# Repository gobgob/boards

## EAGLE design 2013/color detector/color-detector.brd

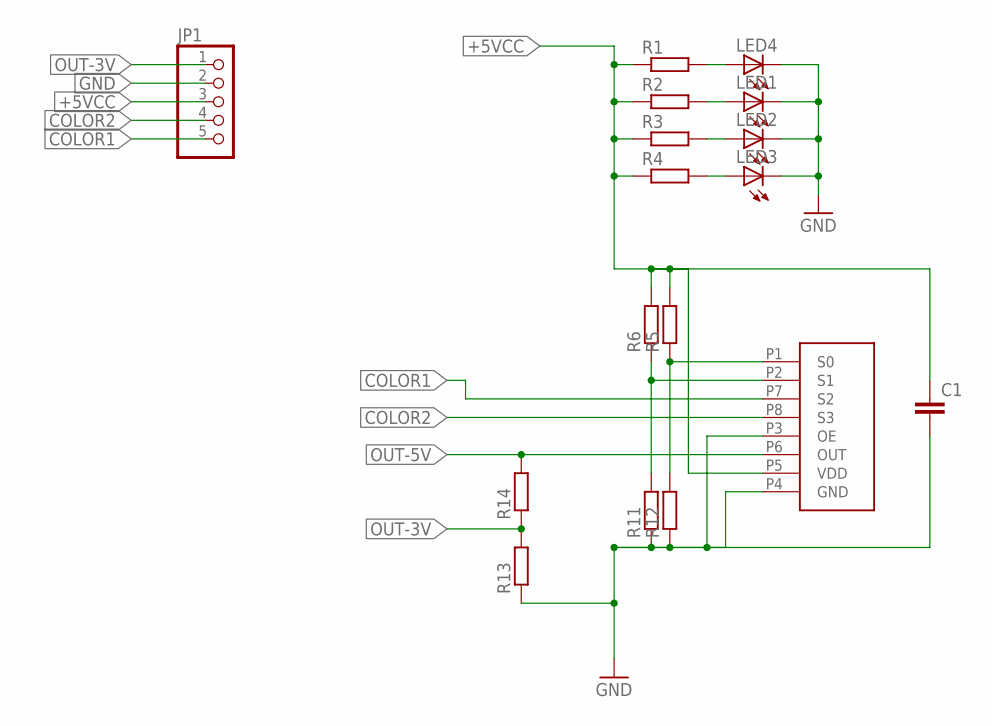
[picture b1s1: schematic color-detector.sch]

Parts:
C1: C-EUC0805; C0805
JP1: PINHD-1X5/90; 1X05/90
LED1, LED2, LED3, LED4: LED3MM
R1, R2, R3, R4, R13, R14: R-EU_R0805; R0805
R5, R6, R11, R12: R-EU_R0402; R0402
U$1: TCS3200; SOIC8

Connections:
+5VCC: C1.1, JP1.3, R1.1, R2.1, R3.1, R4.1, R5.2, R6.2, U$1.P5 (VDD)
COLOR1: JP1.5, U$1.P7 (S2)
COLOR2: JP1.4, U$1.P8 (S3)
GND: C1.2, JP1.2, LED1.K (C), LED2.K (C), LED3.K (C), LED4.K (C), R11.1, R12.1, R13.1, U$1.P3 (OE), U$1.P4 (GND)
unnamed: LED4.A, R1.2
unnamed: LED1.A, R2.2
unnamed: LED2.A, R3.2
unnamed: LED3.A, R4.2
unnamed: R5.1, R12.2, U$1.P1 (S0)
unnamed: R6.1, R11.2, U$1.P2 (S1)
OUT-3V: JP1.1, R13.2, R14.1
OUT-5V: R14.2, U$1.P6 (OUT)

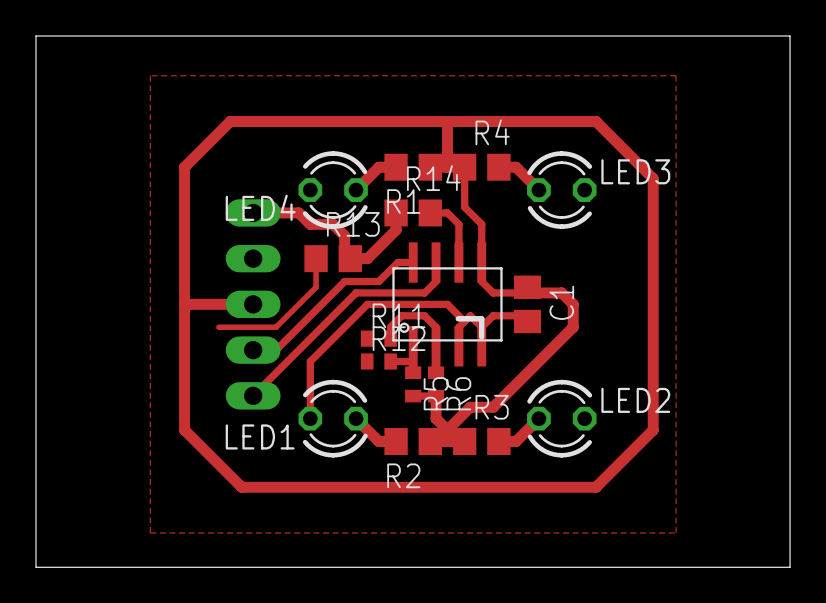
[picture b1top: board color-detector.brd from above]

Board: 2 copper layers, 41.9 x 29.5 mm, 17 parts (1 on the bottom side), 12 nets.

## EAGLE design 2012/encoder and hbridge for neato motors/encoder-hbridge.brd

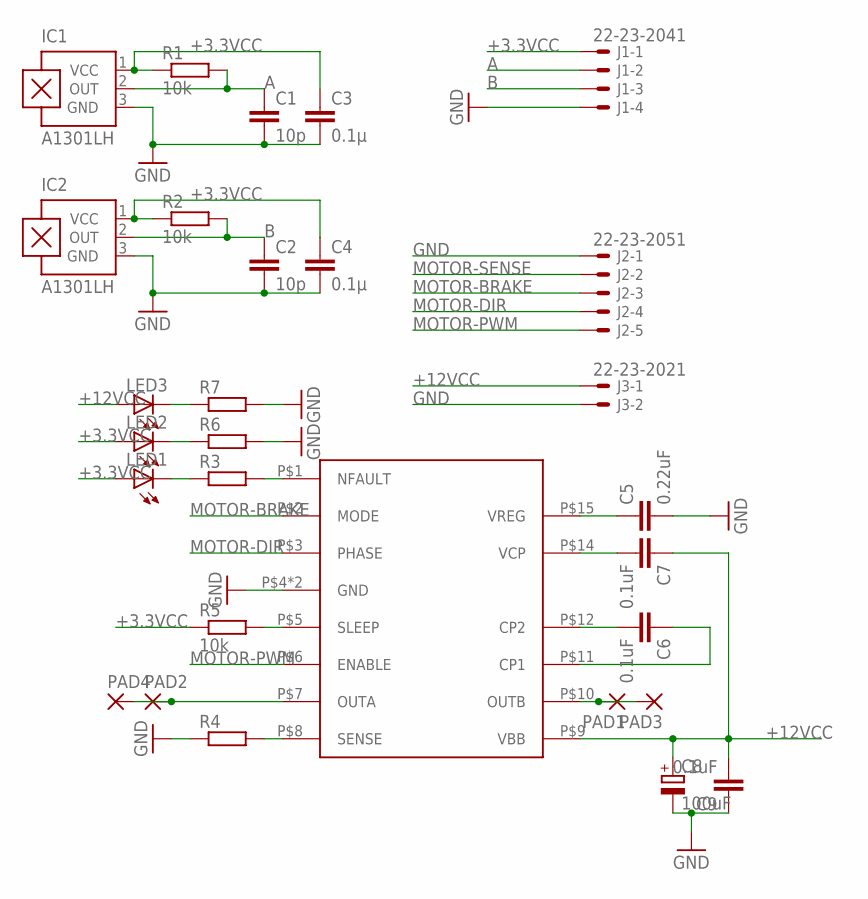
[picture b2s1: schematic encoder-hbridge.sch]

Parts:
C1, C2: 10p; C0805
C3, C4: 0.1µ; C0805
C5: 0.22uF; C0805
C6, C7, C9: 0.1uF; C0805
C8: 100uF; E3,5-8
IC1, IC2: A1301LH; SOT23-W
J1: 22-23-2041
J2: 22-23-2051
J3: 22-23-2021
LED1, LED2, LED3: LED3MM
PAD1, PAD2, PAD3, PAD4: 3,81/1,4
R1, R2, R5: 10k; R0805
R3, R4, R6, R7: R-EU_R0805; R0805
U$1: A3950-DIL; DIL16

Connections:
+3.3VCC: C3.1, C4.1, IC1.1 (VCC), IC2.1 (VCC), J1.1, LED1.A, LED2.A, R1.1, R2.1, R5.1
+12VCC: C7.1, C8.+, C9.2, J3.1, LED3.A, U$1.P$9 (VBB)
A: C1.1, IC1.2 (OUT), J1.2, R1.2
B: C2.1, IC2.2 (OUT), J1.3, R2.2
GND: C1.2, C2.2, C3.2, C4.2, C5.2, C8.-, C9.1, IC1.3 (GND), IC2.3 (GND), J1.4, J2.1, J3.2, R4.1, R6.2, R7.2, U$1.P$4 (GND), U$1.P$13 (GND)
MOTOR-BRAKE: J2.3, U$1.P$2 (MODE)
MOTOR-DIR: J2.4, U$1.P$3 (PHASE)
MOTOR-PWM: J2.5, U$1.P$6 (ENABLE)
MOTOR-SENSE: J2.2
unnamed: C5.1, U$1.P$15 (VREG)
unnamed: C6.2, U$1.P$12 (CP2)
unnamed: C6.1, U$1.P$11 (CP1)
unnamed: C7.2, U$1.P$14 (VCP)
unnamed: PAD1.1, PAD3.1, U$1.P$10 (OUTB)
unnamed: R3.2, U$1.P$1 (NFAULT)
unnamed: LED1.K (C), R3.1
unnamed: R4.2, U$1.P$8 (SENSE)
unnamed: R5.2, U$1.P$5 (SLEEP)
unnamed: LED3.K (C), R7.1
unnamed: LED2.K (C), R6.1
unnamed: PAD2.1, PAD4.1, U$1.P$7 (OUTA)

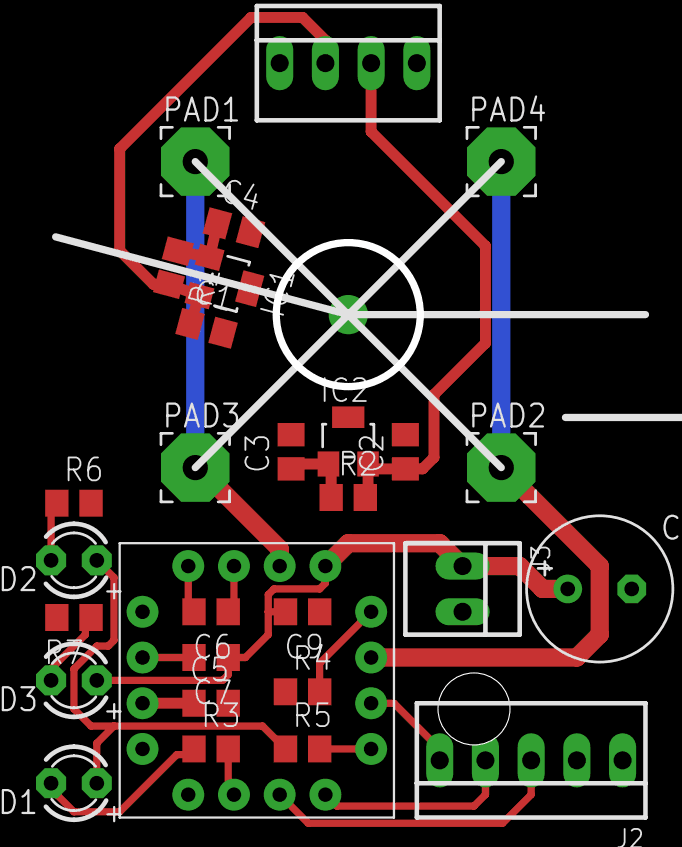
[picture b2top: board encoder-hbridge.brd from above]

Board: 2 copper layers, 29 parts (0 on the bottom side), 20 nets.

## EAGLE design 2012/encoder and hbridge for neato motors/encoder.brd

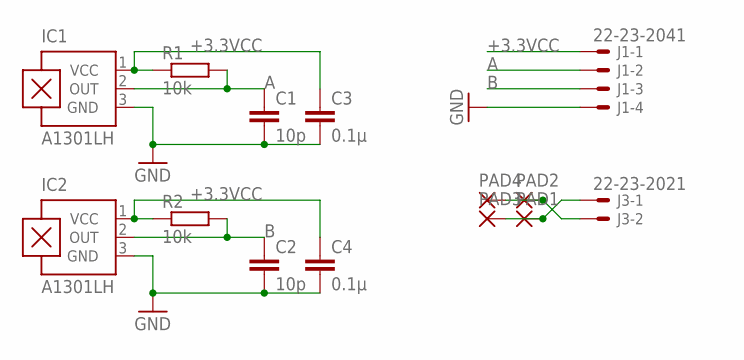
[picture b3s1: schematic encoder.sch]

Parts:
C1, C2: 10p; C0805
C3, C4: 0.1µ; C0805
IC1, IC2: A1301LH; SOT23-W
J1: 22-23-2041
J3: 22-23-2021
PAD1, PAD2, PAD3, PAD4: 3,81/1,4
R1, R2: 10k; R0805

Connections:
+3.3VCC: C3.1, C4.1, IC1.1 (VCC), IC2.1 (VCC), J1.1, R1.1, R2.1
A: C1.1, IC1.2 (OUT), J1.2, R1.2
B: C2.1, IC2.2 (OUT), J1.3, R2.2
GND: C1.2, C2.2, C3.2, C4.2, IC1.3 (GND), IC2.3 (GND), J1.4
unnamed: J3.1, PAD1.1, PAD3.1
unnamed: J3.2, PAD2.1, PAD4.1

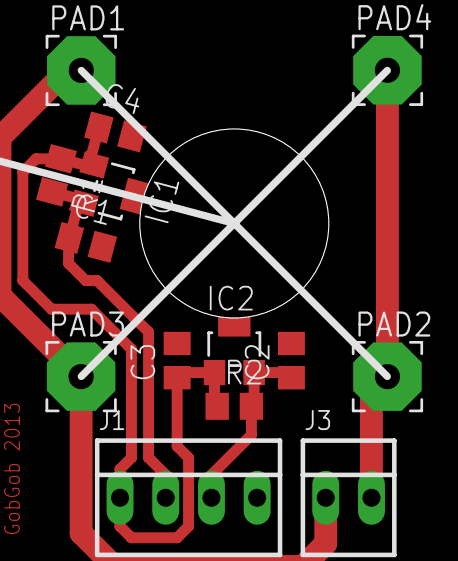
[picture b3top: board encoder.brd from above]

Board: 4 copper layers, 14 parts (0 on the bottom side), 6 nets.

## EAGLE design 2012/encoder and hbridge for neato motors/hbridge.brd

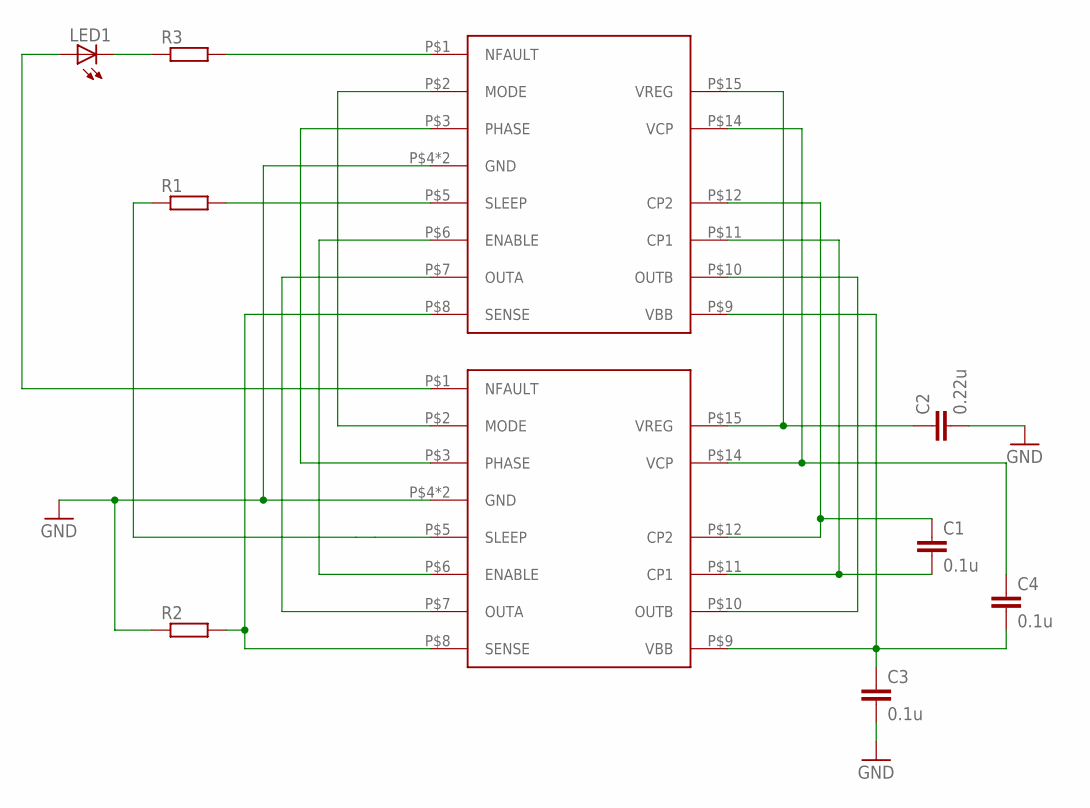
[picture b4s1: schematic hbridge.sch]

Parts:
C1, C3, C4: 0.1u; C0603
C2: 0.22u; C0603
LED1: LED3MM
R1, R2, R3: R-EU_R0603; R0603
U$1: A3950; 16TSSOP
U$2: A3950-DIL; DIL16

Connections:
GND: C2.2, C3.2, R2.1, U$1.P$4 (GND), U$1.P$13 (GND), U$2.P$4 (GND), U$2.P$13 (GND)
unnamed: LED1.A, U$2.P$1 (NFAULT)
unnamed: U$1.P$2 (MODE), U$2.P$2 (MODE)
unnamed: U$1.P$3 (PHASE), U$2.P$3 (PHASE)
unnamed: R1.2, U$1.P$5 (SLEEP)
unnamed: U$1.P$6 (ENABLE), U$2.P$6 (ENABLE)
unnamed: U$1.P$7 (OUTA), U$2.P$7 (OUTA)
unnamed: R2.2, U$1.P$8 (SENSE), U$2.P$8 (SENSE)
unnamed: C2.1, U$1.P$15 (VREG), U$2.P$15 (VREG)
unnamed: C4.1, U$1.P$14 (VCP), U$2.P$14 (VCP)
unnamed: R1.1, U$2.P$5 (SLEEP)
unnamed: C1.1, U$1.P$12 (CP2), U$2.P$12 (CP2)
unnamed: C1.2, U$1.P$11 (CP1), U$2.P$11 (CP1)
unnamed: U$1.P$10 (OUTB), U$2.P$10 (OUTB)
unnamed: C3.1, C4.2, U$1.P$9 (VBB), U$2.P$9 (VBB)
unnamed: LED1.K (C), R3.1
unnamed: R3.2, U$1.P$1 (NFAULT)

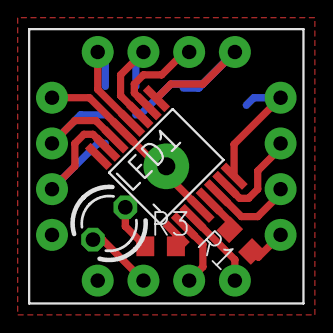
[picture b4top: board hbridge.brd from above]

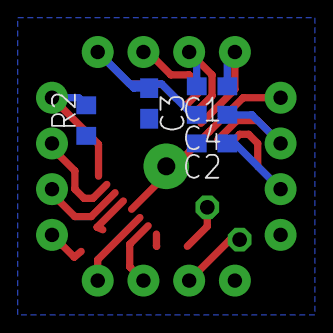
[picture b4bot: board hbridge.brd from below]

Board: 2 copper layers, 10 parts (5 on the bottom side), 17 nets.

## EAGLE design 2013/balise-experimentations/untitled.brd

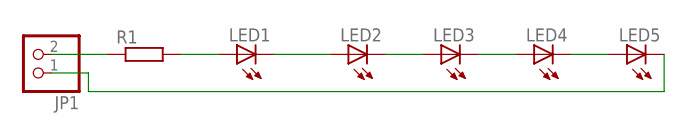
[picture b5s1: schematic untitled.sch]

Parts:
JP1: PINHD-1X2/90; 1X02/90
LED1, LED2, LED3, LED4, LED5: LED5MM
R1: R-EU_0204/2V; 0204V

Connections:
unnamed: LED4.K (C), LED5.A
unnamed: LED3.K (C), LED4.A
unnamed: LED2.K (C), LED3.A
unnamed: JP1.2, R1.1
unnamed: LED1.A, R1.2
unnamed: LED1.K (C), LED2.A
unnamed: JP1.1, LED5.K (C)

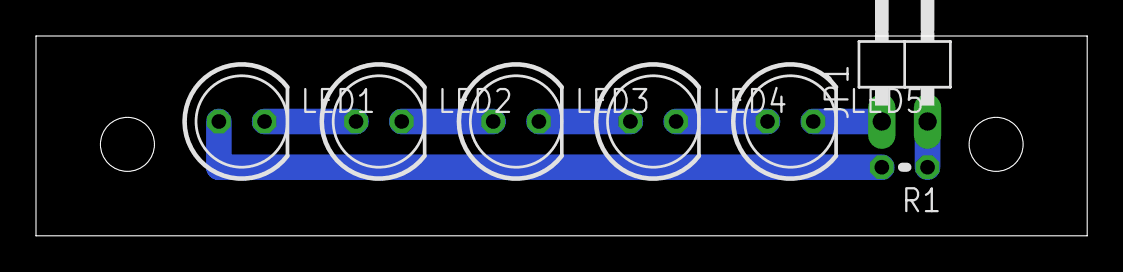
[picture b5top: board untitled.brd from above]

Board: 2 copper layers, 58.4 x 11.1 mm, 7 parts (0 on the bottom side), 7 nets.

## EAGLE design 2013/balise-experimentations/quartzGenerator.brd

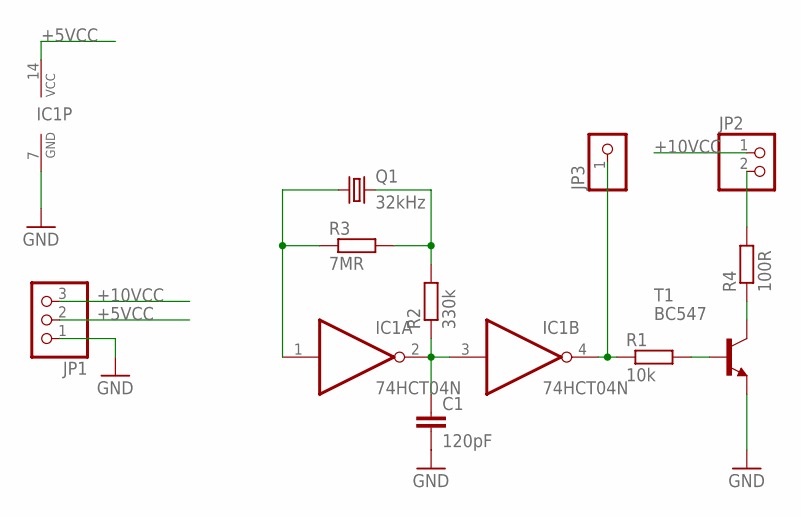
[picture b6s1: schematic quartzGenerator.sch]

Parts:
C1: 120pF; C050-030X075
IC1: 74HCT04N; DIL14
JP1: PINHD-1X3; 1X03
JP2: PINHD-1X2; 1X02
JP3: PINHD-1X1; 1X01
Q1: 32kHz; TC26H
R1: 10k; 0207/7
R2: 330k; 0207/7
R3: 7MR; 0207/7
R4: 100R; 0207/7
T1: BC547; TO92

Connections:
+5VCC: IC1.14 (VCC), JP1.2
+10VCC: JP1.3, JP2.1
GND: C1.2, IC1.7 (GND), JP1.1, T1.1 (E)
unnamed: IC1.1 (I), Q1.1, R3.1
unnamed: C1.1, IC1.2 (O), IC1.3 (I), R2.1
unnamed: Q1.2, R2.2, R3.2
unnamed: IC1.4 (O), JP3.1, R1.1
unnamed: R1.2, T1.2 (B)
unnamed: R4.1, T1.3 (C)
unnamed: JP2.2, R4.2

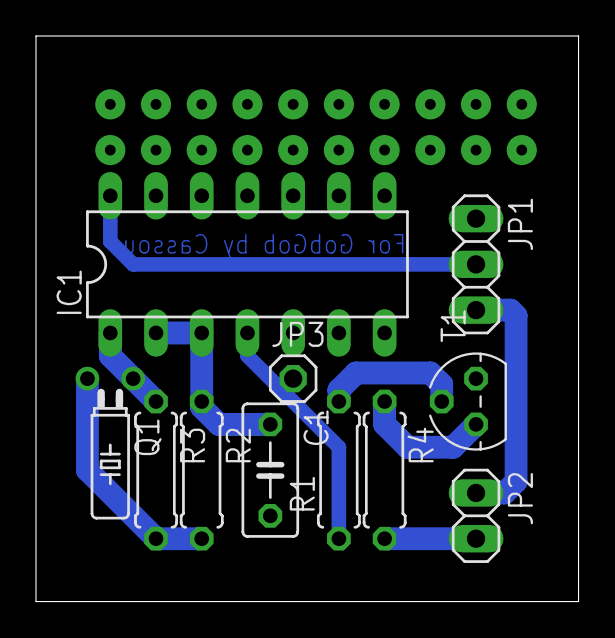
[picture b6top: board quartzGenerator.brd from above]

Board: 2 copper layers, 30.1 x 31.4 mm, 11 parts (0 on the bottom side), 10 nets.

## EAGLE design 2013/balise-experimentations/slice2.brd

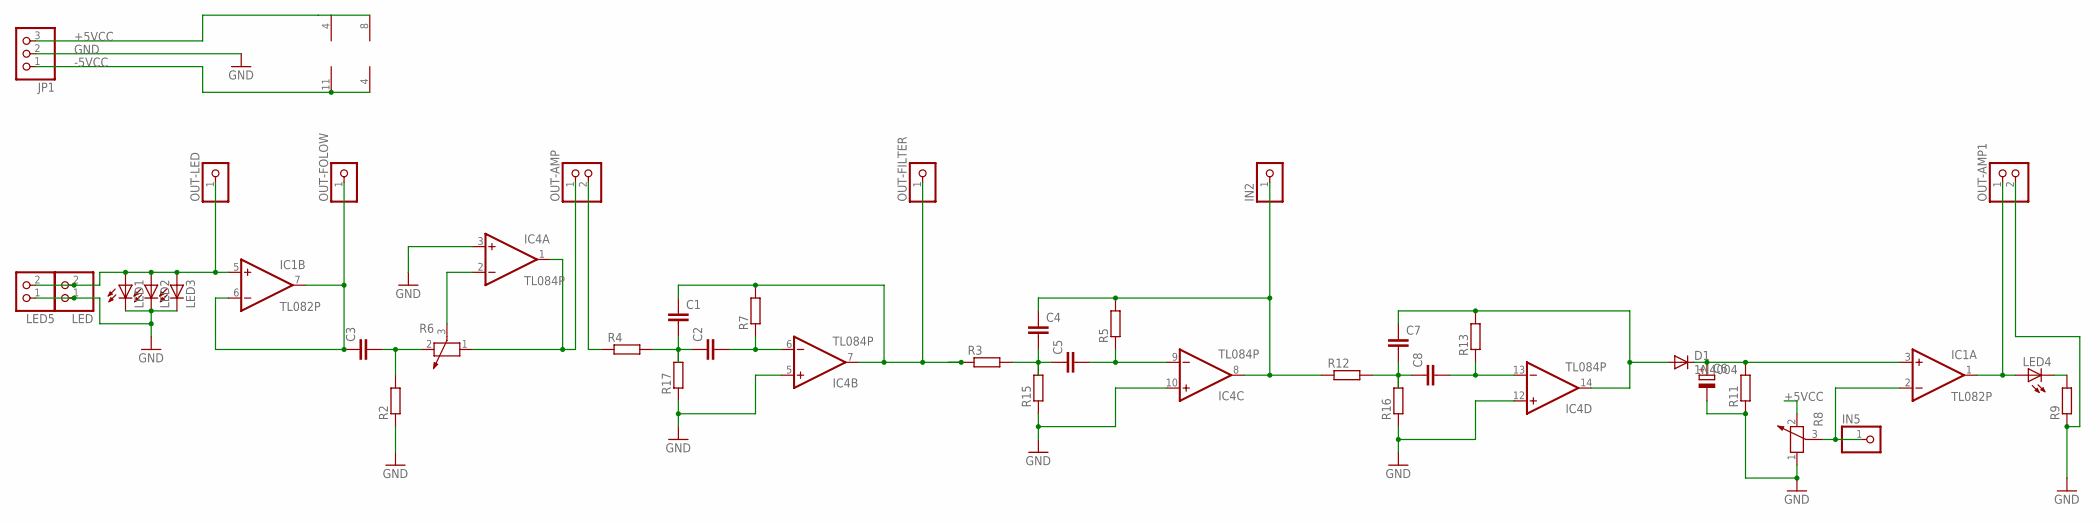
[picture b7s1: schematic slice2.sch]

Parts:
C1, C2, C3, C4, C5, C7, C8: C-EU050-024X044; C050-024X044
C6: CPOL-EUE3.5-8; E3,5-8
D1: 1N4004; DO41-10
IC1: TL082P; DIL08
IC4: TL084P; DIL14
IN2, IN5: PINHD-1X1; 1X01
JP1: PINHD-1X3; 1X03
LED, LED5: PINHD-1X2; 1X02
LED1, LED2, LED3, LED4: LED5MM
OUT-AMP, OUT-AMP1: PINHD-1X2; 1X02
OUT-FILTER: PINHD-1X1; 1X01
OUT-FOLOW: PINHD-1X1; 1X01
OUT-LED: PINHD-1X1; 1X01
R2, R3, R4, R5, R7, R9, R11, R12, R13, R15, R16, R17: R-EU_0204/7; 0204/7
R6, R8: POTENTIOMETER_PT-10; PT-10

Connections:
+5VCC: IC1.8 (V+), IC4.4 (V+), JP1.3, R8.2
-5VCC: IC1.4 (V-), IC4.11 (V-), JP1.1
GND: C6.-, IC4.3 (+IN), IC4.5 (+IN), IC4.10 (+IN), IC4.12 (+IN), JP1.2, LED.1, LED1.K (C), LED2.K (C), LED3.K (C), LED5.1, OUT-AMP1.2, R2.1, R8.1, R9.1, R11.1, R15.1, R16.1, R17.1
unnamed: OUT-AMP.2, R4.1
unnamed: C3.2, R2.2, R6.2
unnamed: C6.+, D1.C, IC1.3 (+IN), R11.2
unnamed: IC1.1 (OUT), LED4.A, OUT-AMP1.1
unnamed: C7.2, C8.1, R12.2, R16.2
unnamed: C7.1, D1.A, IC4.14 (OUT), R13.2
unnamed: C8.2, IC4.13 (-IN), R13.1
unnamed: C4.1, IC4.8 (OUT), IN2.1, R5.2, R12.1
unnamed: C4.2, C5.1, R3.2, R15.2
unnamed: C5.2, IC4.9 (-IN), R5.1
unnamed: C1.1, IC4.7 (OUT), OUT-FILTER.1, R3.1, R7.2
unnamed: IC1.5 (+IN), LED.2, LED1.A, LED2.A, LED3.A, LED5.2, OUT-LED.1
unnamed: C3.1, IC1.6 (-IN), IC1.7 (OUT), OUT-FOLOW.1
unnamed: IC4.2 (-IN), R6.3
unnamed: IC4.1 (OUT), OUT-AMP.1, R6.1
unnamed: C1.2, C2.1, R4.2, R17.2
unnamed: C2.2, IC4.6 (-IN), R7.1
unnamed: IC1.2 (-IN), IN5.1, R8.3
unnamed: LED4.K (C), R9.2

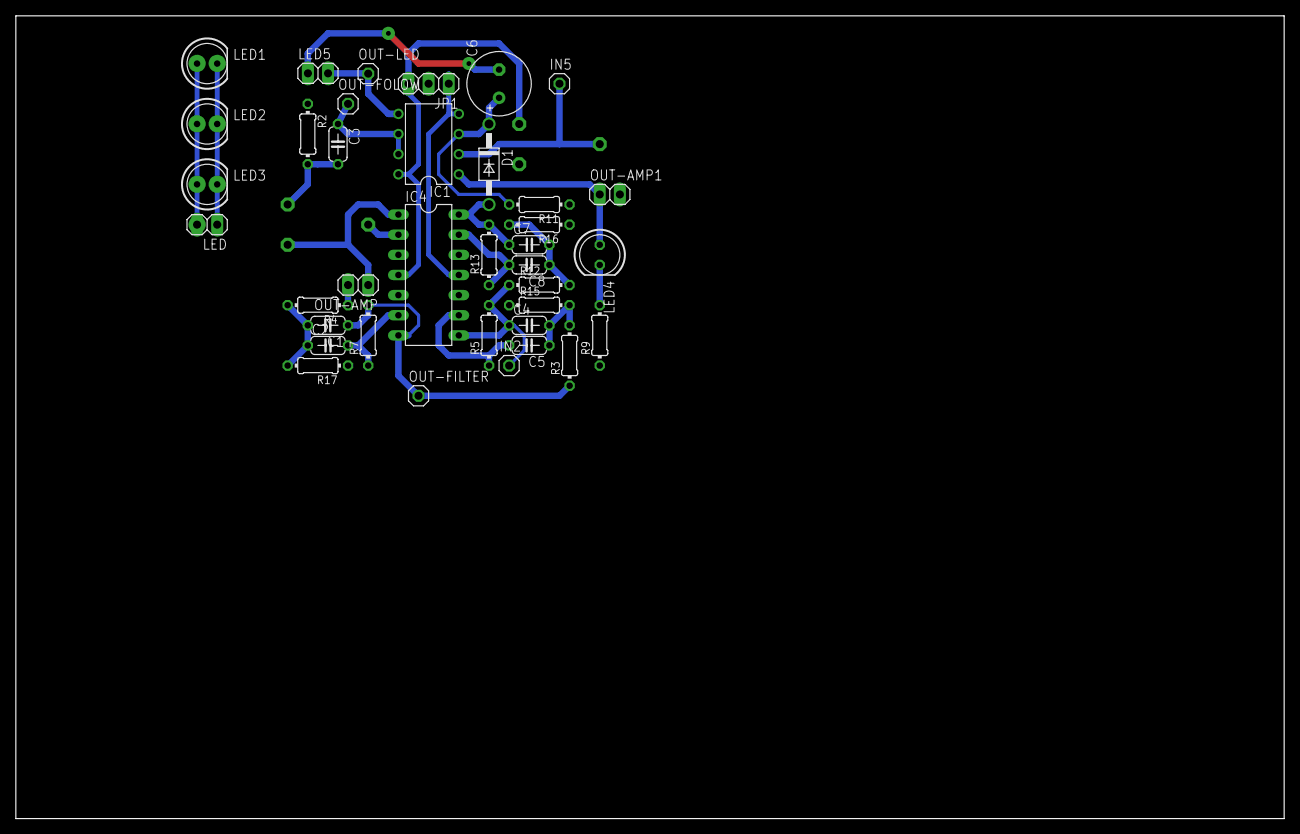
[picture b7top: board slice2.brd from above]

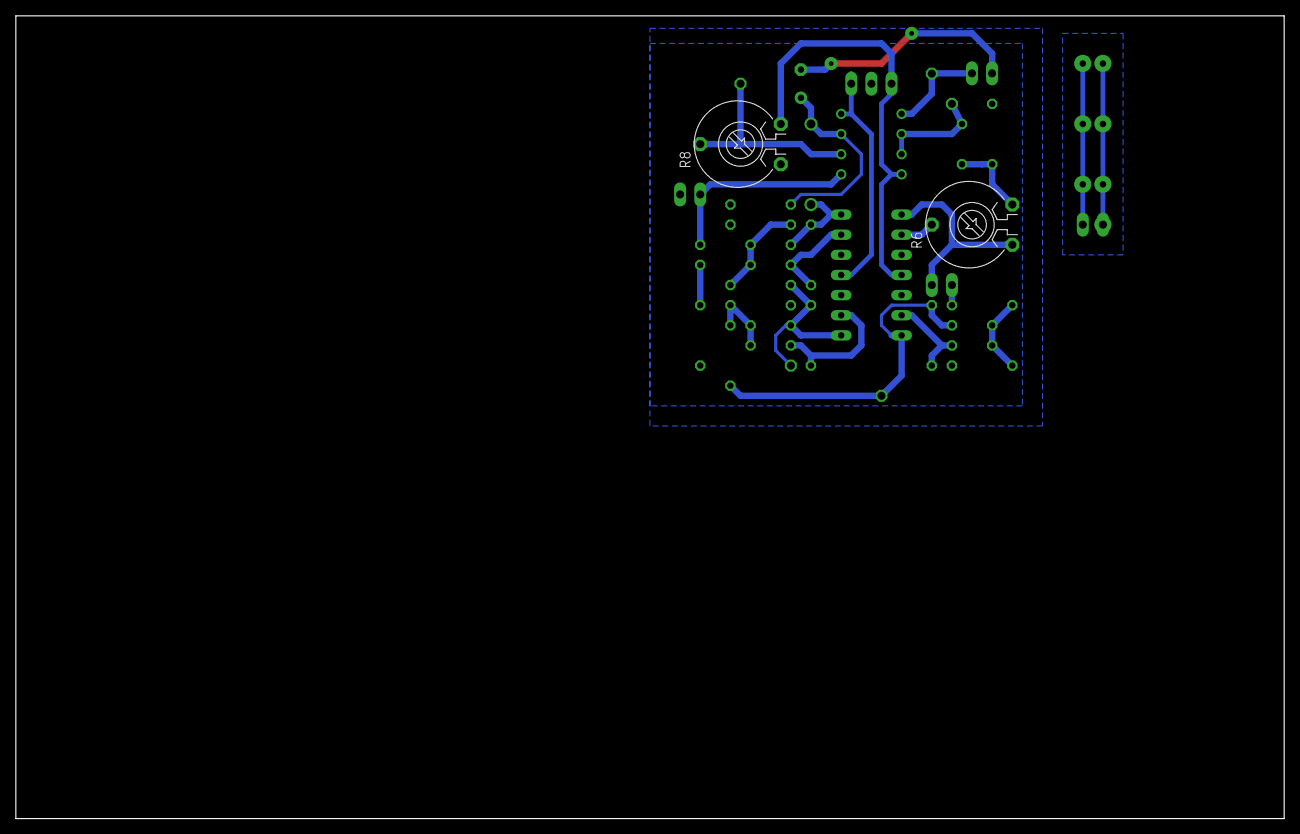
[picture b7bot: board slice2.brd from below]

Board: 2 copper layers, 160.0 x 101.3 mm, 39 parts (2 on the bottom side), 22 nets.

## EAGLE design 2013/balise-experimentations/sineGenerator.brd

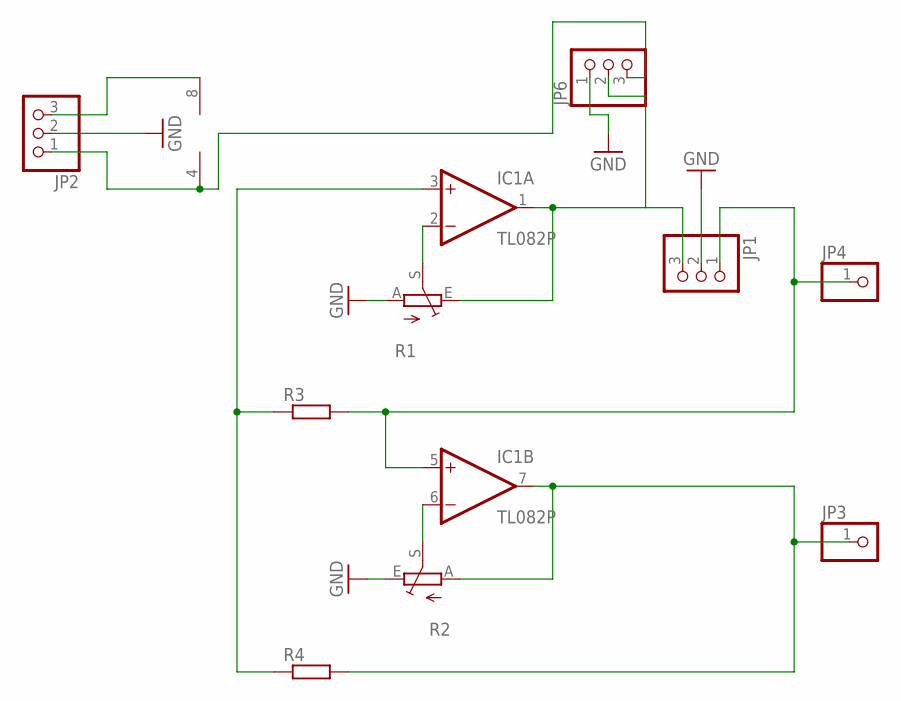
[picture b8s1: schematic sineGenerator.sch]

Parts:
IC1: TL082P; DIL08
JP1, JP2, JP6: PINHD-1X3; 1X03
JP3, JP4: PINHD-1X1; 1X01
R1, R2: TRIM_EU-CA9V; CA9V
R3, R4: R-EU_0204/2V; 0204V

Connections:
GND: JP1.2, JP2.2, JP6.1, R1.A, R2.E
unnamed: IC1.8 (V+), JP2.3
unnamed: IC1.4 (V-), JP2.1, JP6.3
unnamed: IC1.1 (OUT), JP1.3, JP6.2, R1.E
unnamed: IC1.2 (-IN), R1.S
unnamed: IC1.3 (+IN), R3.1, R4.1
unnamed: IC1.6 (-IN), R2.S
unnamed: IC1.5 (+IN), JP1.1, JP4.1, R3.2
unnamed: IC1.7 (OUT), JP3.1, R2.A, R4.2

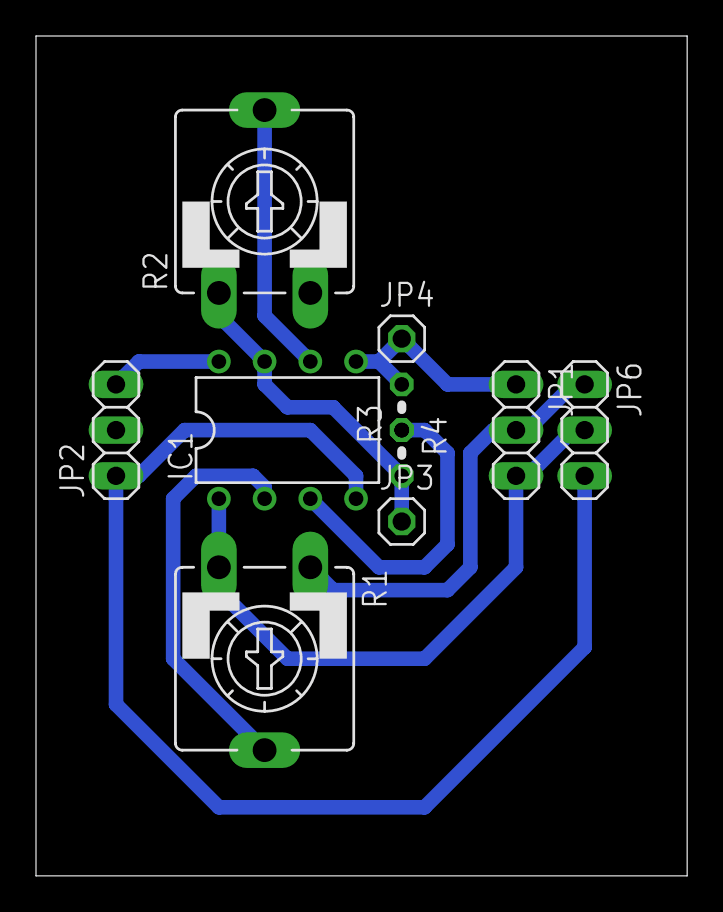
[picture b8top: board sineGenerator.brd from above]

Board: 2 copper layers, 36.2 x 46.7 mm, 10 parts (0 on the bottom side), 9 nets.

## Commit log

2015-01-31 Bigger +5v
2015-01-31 Add a teensy adaptor v1
2015-02-01 Teensy adaptor v2
2015-02-01 Teensy adaptor v3
2015-02-01 Add an optional second alim
2015-02-15 Pinswap 5v - signal + DRU OK
2015-02-15 Condo party!!!! \o/
2015-03-01 Update minionRVB
2015-03-01 move boards
2015-03-01 prepare for manufacturing
2015-04-06 add files sent to seedstudio for manuf
2015-04-06 Move to subfolder
2015-04-06 Add some code to control the eye
2015-04-18 Add display_color
2015-04-18 Limit luminosity
2015-04-18 Fix luminosity fail
2015-04-19 Global refactor
    frame to sprite
    offset_x and offset_y optionnals parameters into display_sprite
    add display row and line
    comment and rearrange all
2015-04-19 Add K2000 animation
2015-04-19 Add a loop option
2015-04-19 Add heart animation
2015-04-19 Fix doc
2015-04-19 Clap animation
2015-04-19 Ajust clap animation
2015-04-19 Add makeColor utility
2015-04-19 Add a rainbow animation
2015-04-19 Remove useless things
2015-04-19 Turn display sprite
2015-04-19 Display text
2015-04-20 Add all letters sprite
2015-04-20 Add a color option on display text
2015-04-20 Update example
2015-04-25 Fix compilations errors
2015-04-26 Improve sprites and letters memory management
2015-04-26 Add MIN & MAX utilities
2015-04-26 Define eyes ports and leds count
2015-04-26 Add eye_port option to display sprite
2015-04-26 Display text on 2 eyes
2015-04-26 Variabilize text begin offset
2015-04-27 Make luminosity settable
2015-04-27 Add some spaces
2015-04-27 SILON animation
2015-04-27 Add eye_port option
2015-04-27 No more `leds.show()` into core function to have more controls outside
2015-04-28 Eyes animation (with multilayers \o/)
2015-05-02 Update lid animation
2015-05-02 Reindent & refactor all anims into 2 eyes mode
2015-05-02 Update display_row
2015-05-02 Add clear() method
2015-05-02 Update animation using display_row
2015-05-02 Add Text functionnality
2015-05-02 Update animation policy
2015-05-03 Add flash
2015-05-04 Look right and left animation
2015-05-05 Refactor name and typo (camelCase instead of snake_case)
2015-05-05 More debug
2015-05-05 Lib python
2015-05-06 Add numbers sprites
2015-05-06 Add countdown animation
2015-05-09 Simple pacman animation
2015-05-13 Add `addColorSprite` utility
2015-05-13 Update pacman animation
2015-05-13 Add robot color method
2015-05-13 start fixing for python 3
2015-05-13 Update lib to python 3
2017-01-07 add 2014 boards
2017-01-07 add balise experimentations
2017-01-07 add encoder and hbridge for neato motors
2017-01-07 add harp receptor board
2017-01-07 add color detector board
